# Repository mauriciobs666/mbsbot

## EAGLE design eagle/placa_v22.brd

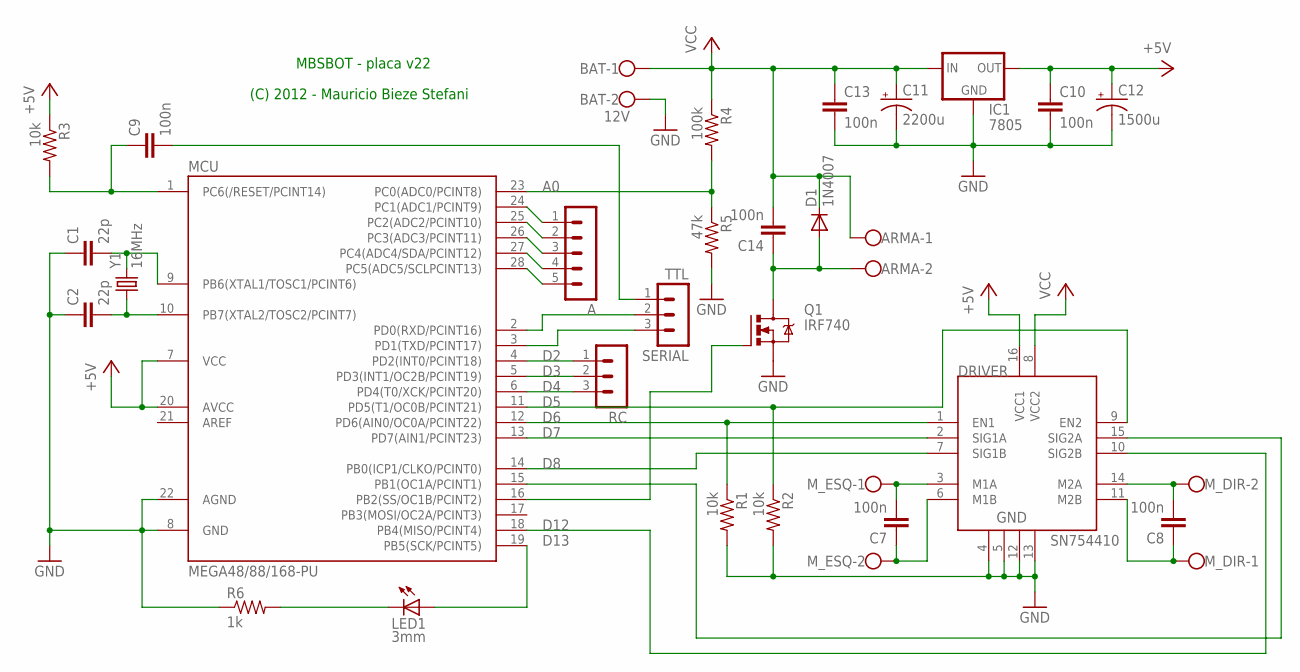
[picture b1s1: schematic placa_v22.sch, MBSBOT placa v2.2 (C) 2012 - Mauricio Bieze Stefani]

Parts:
A: MA05-1
ARMA: W237-102
BAT: 12V; W237-102; MPN 237-102
C1, C2: 22p; CAP-PTH-SMALL-KIT
C7, C8, C9, C10, C13, C14: 100n; CAP-PTH-5MM
C11: 2200u; CPOL-RADIAL-100UF-25V
C12: 1500u; CPOL-RADIAL-100UF-25V
D1: 1N4007; DIODE-1N4001
DRIVER: SN754410; DIP16
IC1: 7805; 78XXS
LED1: 3mm; LED3MM
MCU: MEGA48/88/168-PU; DIL28-3
M_DIR: W237-102
M_ESQ: W237-102
Q1: IRF740; TO220BV
R1, R2, R3: 10k; AXIAL-0.5
R4: 100k; AXIAL-0.5
R5: 47k; AXIAL-0.5
R6: 1k; AXIAL-0.3-KIT
RC: MA03-1
SERIAL: TTL; MA03-1
Y1: 16MHz; HC49US

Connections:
+5V: C10.1, C12.1 (+), DRIVER.16 (VCC1), IC1.OUT, MCU.7 (VCC), MCU.20 (AVCC), R3.P$1 (1)
A: MCU.2 (PD0(RXD/PCINT16)), SERIAL.2
A0: MCU.23 (PC0(ADC0/PCINT8)), R4.P$2 (2), R5.P$1 (1)
D2: MCU.4 (PD2(INT0/PCINT18)), RC.1
D3: MCU.5 (PD3(INT1/OC2B/PCINT19)), RC.2
D4: MCU.6 (PD4(T0/XCK/PCINT20)), RC.3
D5: DRIVER.9 (EN2), MCU.11 (PD5(T1/OC0B/PCINT21)), R2.P$1 (1)
D6: DRIVER.1 (EN1), MCU.12 (PD6(AIN0/OC0A/PCINT22)), R1.P$1 (1)
D7: DRIVER.2 (SIG1A), MCU.13 (PD7(AIN1/PCINT23))
D8: DRIVER.7 (SIG1B), MCU.14 (PB0(ICP1/CLKO/PCINT0))
D12: DRIVER.10 (SIG2B), MCU.18 (PB4(MISO/PCINT4))
D13: LED1.A, MCU.19 (PB5(SCK/PCINT5))
GND: BAT.2, C1.1, C2.1, C10.2, C11.2 (-), C12.2 (-), C13.2, DRIVER.4, DRIVER.5, DRIVER.12, DRIVER.13, IC1.GND, MCU.8 (GND), MCU.22 (AGND), Q1.S, R1.P$2 (2), R2.P$2 (2), R5.P$2 (2), R6.P$1 (1)
unnamed: LED1.K (C), R6.P$2 (2)
unnamed: C9.1, MCU.1 (PC6(/RESET/PCINT14)), R3.P$2 (2)
unnamed: C1.2, MCU.9 (PB6(XTAL1/TOSC1/PCINT6)), Y1.2
unnamed: C2.2, MCU.10 (PB7(XTAL2/TOSC2/PCINT7)), Y1.1
unnamed: C7.2, DRIVER.3 (M1A), M_ESQ.1
unnamed: C7.1, DRIVER.6 (M1B), M_ESQ.2
unnamed: C8.1, DRIVER.11 (M2B), M_DIR.1
unnamed: C8.2, DRIVER.14 (M2A), M_DIR.2
unnamed: MCU.3 (PD1(TXD/PCINT17)), SERIAL.3
unnamed: C9.2, SERIAL.1
unnamed: ARMA.2, C14.1, D1.A, Q1.D
unnamed: A.1, MCU.24 (PC1(ADC1/PCINT9))
unnamed: A.2, MCU.25 (PC2(ADC2/PCINT10))
unnamed: A.3, MCU.26 (PC3(ADC3/PCINT11))
unnamed: A.4, MCU.27 (PC4(ADC4/SDA/PCINT12))
unnamed: A.5, MCU.28 (PC5(ADC5/SCLPCINT13))
unnamed: MCU.16 (PB2(SS/OC1B/PCINT2)), Q1.G
unnamed: DRIVER.15 (SIG2A), MCU.15 (PB1(OC1A/PCINT1))
VCC: ARMA.1, BAT.1, C11.1 (+), C13.1, C14.2, D1.C, DRIVER.8 (VCC2), IC1.IN, R4.P$1 (1)

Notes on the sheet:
(C) 2012 - Mauricio Bieze Stefani
MBSBOT - placa v22

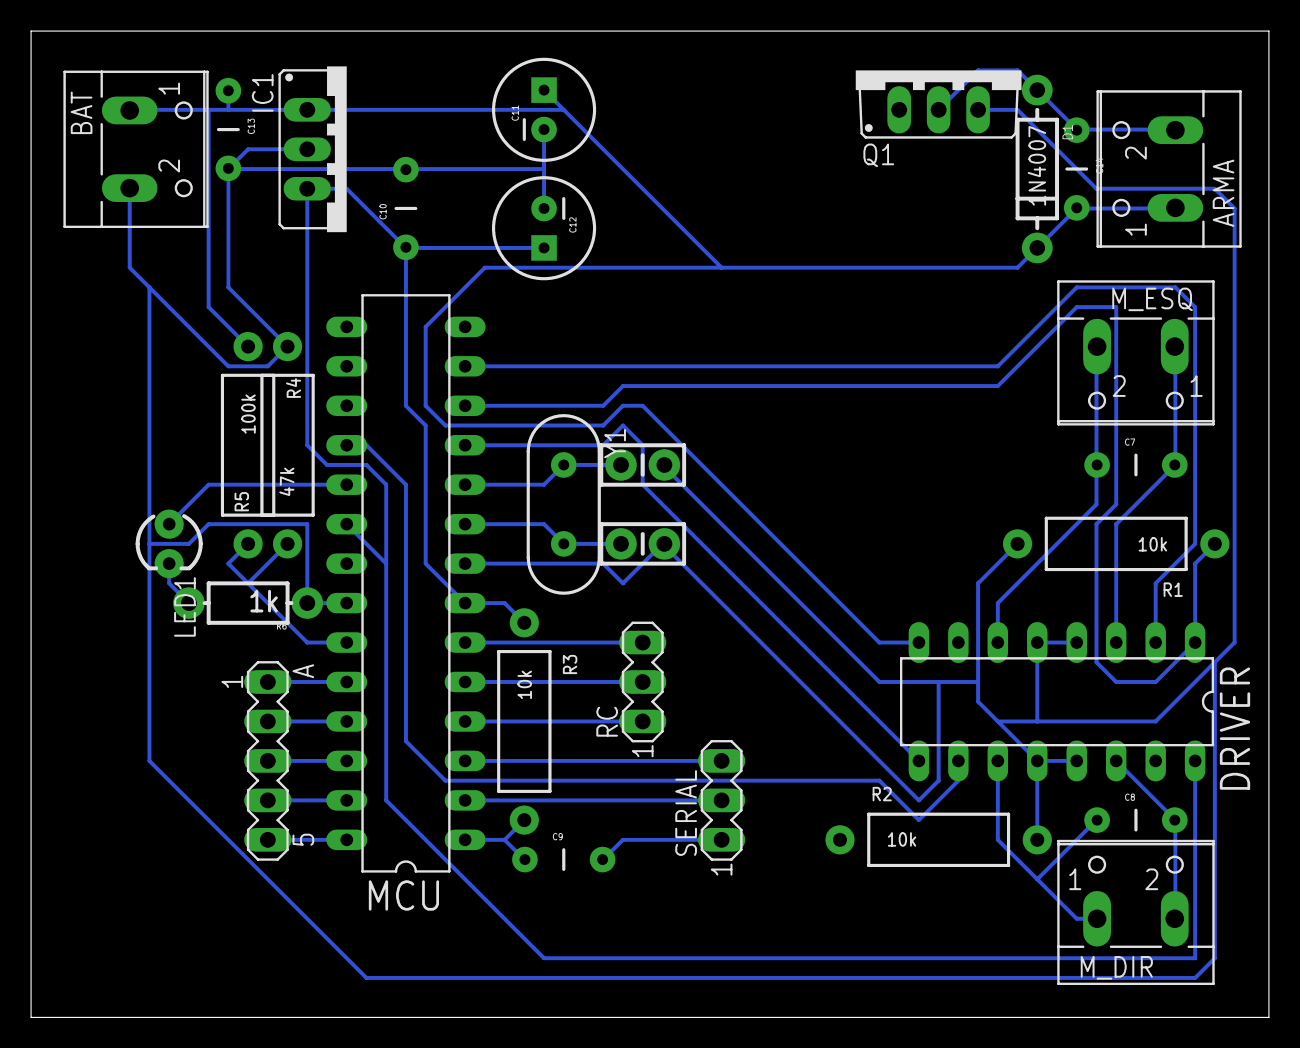
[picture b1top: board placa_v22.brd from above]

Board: 2 copper layers, 79.7 x 63.5 mm, 30 parts (0 on the bottom side), 32 nets.

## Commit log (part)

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2010-03-29 Interface improvements.
2010-04-07 Added average function to sensor analysis tab.
2010-04-08 Visual changes
2010-04-09 Added workspace
2010-04-09 Removed the preferences window. All configuration should be done in the SETUP tab.
2010-04-09 Change average algorithm to calc only last 10 measures.
2010-04-11 New prog to test 754410 chip.
2010-04-14 Small changes in the motor control shield
2010-04-15 WheelDC and drive by joystick fully working
2010-04-15 Visual and comments
2010-04-17 Small typo
2010-04-23 Unlocked full DC motor power (PWM 250). Started implementing keyboard control (core dump).
2010-05-02 Fixec core dump.
2010-05-17 Comments
2010-05-18 Missing file
2010-05-18 Improvements on joystick control Bugfixes
2010-05-18 Damn fucking servo library bitch!!!
2010-05-21 Changed DC motor pins to avoid conflict with servo lib
2010-05-21 Removed obsolet 754410 test prog Added old (arduino < 16) servo library in the hope the servo will stop jittering.
2010-05-29 Partial move files
2010-05-29 Moving files
2010-05-30 Rangefinder improvements
2010-06-01 bug fixes
2010-06-11 Created include to configure board pins
2010-06-19 Better comments.
2010-06-21 defines and comments
2010-06-22 Moved vectorial drive logic to firmware
2010-06-24 First PID scratch
2010-06-24 More PID control stuff
2010-07-01 Created new collision detector
2010-07-01 Collision detection implementation
2010-08-23 IR 5 sensor board
2010-08-31 Small details. Auto fetch status.
2010-09-02 Joystick calibration
2010-09-04 Average class
2010-09-04 Acceleration
2010-09-05 GUI improvements
2010-09-08 Bugfixes
2010-09-09 New commands left, right and set dr.
2010-09-15 Moved average to MBSUtil
2010-09-16 Program SENTRY
2010-10-14 Computer vision using OpenCV 2.1
2010-10-15 Update windows project
2010-10-17 Better timing
2010-10-25 Various
2010-10-29 Fixed servo bug
2010-11-03 Partial implementation of second and third servos.
2010-11-04 Fixed visual bug. Implemented mltiple servos in arduino side (untested).
2010-11-04 Gambiarra 2/2 (removed executable attribute from Protocol.h)
2010-11-04 QRD1114
2010-11-07 Finally able to make the wiichuck work :-)
2010-11-12 Wiichuck now able to pan & tilt servos.
2010-11-12 Various small optimizations and fixes.
2010-11-14 Bugfixes in nunchuck. Rewrote vectorial drive.
2010-11-18 Generate sensor data for "Processing" example
2010-11-22 Visual changes. New hand brake function. Placed pull down resistors on 754410 to avoid movement during start-up.
2010-11-23 Joystick handling improvements.
2010-11-24 Joystick...
2010-11-27 New widgets
2010-12-10 Removed Arduino EEPROM library dependency.
2010-12-28 Reflash script
2011-01-05 Serial port using boost tests
2011-01-05 Learning boost::program_options
2011-01-06 boost::thread
2011-01-12 Miniterminal serial fully functional (sync/thread).
2011-01-13 Threaded version... will it ever work?
2011-02-01 Arduino oscilloscope viewer
2011-02-01 Windows project
2011-02-06 Laser habilitado. Corrigido controle servos via wiichuck
2011-02-09 Rascunho direcao por wiichuck.
2011-02-10 Arduino library and Codeblocks project
2011-02-15 Removidos delays de PRG_SCOPE
2011-07-03 Pequenos fixes.
2011-11-06 cv windows
2011-11-25 Porting back pra windows 100%. Td funfando.
2011-11-25 Era uma vez um developer maneh que achava que tinha que escrever codigo em ingles. Um dia ele bateu a cabeca e voltou a escrever normal. E viveu feliz pra sempre. The end.
2011-12-07 Porting pra Arduino 1.0
2011-12-11 Depois do que aconteceu na 376346 achei melhor dar um trato no protocolo, falta coisa ainda mas tah bem melhor...
2011-12-18 Faxina
2011-12-20 Aceleracao por software pra simular inercia e tornar o controle mais suave.
2011-12-21 Bugs
2011-12-27 Diversos detalhes
2011-12-28 Muitos bugs depois... Aceleracao e controle vetorial praticamente prontos!!! :-)
2011-12-30 Nova classe Sensor
2012-01-05 Tirei todos warnings e coloquei mais umas coisinhas na classe Sensor.
2012-01-10 Copyright
2012-01-11 Diversos
2012-01-17 Alguns pequenos fixes na classe Sensor (agora funfando belezinha)
2012-01-29 Pequenos ajustes de velocidade
2012-02-01 Bug da foto
2012-02-03 Pequenas mudancas na forma que a atualizacao dos motores eh feita.
2012-02-06 Glitches...
2012-02-09 Os 2 eixos do wxJoystick agora funcionam.
2012-02-13 4 rodas mecanum funfando na gambiarra :-D Precisa rescrever um monte de coisa.
2012-02-13 Limpezinha meia boca
2012-02-28 Add no projeto
2012-03-02 Tava invertido
2012-04-15 Comecei a rescrever tratamento de joystick
2012-05-31 Coisinhas
2012-06-13 Autoversion
2012-06-18 Inicializacao automatica do joystick
2012-06-28 Bugs e to do diversos
2012-06-30 Movida implementacao de joystick pro firmware.
2012-06-30 Mais coisas do joystick
2012-06-30 x86: dropando suporte a CMD_MV_WHEELS, CMD_MV_VECT e classe de joystick. A logica agora fica 100% no firmware.
2012-07-09 Refatoracao
2012-07-10 Mais um pouquinho de refactor
2012-07-11 Projeto eagle Pequenos fixes
2012-07-14 Suporte a controlador de motor sem inversor pras pontes H. Removido variaveis deprecated.
2012-07-14 Faltou pdf...
2012-07-21 Eletronica do Winchester
2012-07-30 bla bla bla
2012-08-03 Bugfix e hardware da arma
2012-08-05 Eletronica
2012-08-09 Boberinhas
2012-08-22 Milhares de fixes
2012-09-11 Nova classe ConfigSensor pra armazenar na EEPROM. Ajustes no circuito e placa.
2012-09-18 Limite de velocidade
2012-09-25 Direcao auxiliada por sensores parcialmente implementada
2012-10-02 Porting pra v2
2012-10-04 Faxinao
2012-10-07 Bugs e reducao de binario
2012-10-09 So close...
2012-10-12 *Bugado
2012-10-14 Coisinhas, ainda bugado
2012-10-18 autoMinMax agora eh configuravel pra poder usar getPorcentoAprox em vetorialSensor
2012-10-24 ConfigGamepad
2013-03-04 Resources
2013-03-06 Bugs <3
2013-03-08 Faxinaum
2013-04-29 Pequenos ajustes da autonavegação via sensor ping
2013-05-08 Nova plava v4, line follower
2013-05-14 Rascunho da calibração da barra de sensores do line follow.
2013-05-17 Calibragem 100% Funçao de mostrar fps
2013-05-23 Bugs marditos
2013-05-27 Proporcional implementado
2013-06-08 Mergeado agrupaLinha com refresh. Muchos bugs...
2013-06-17 struct Grupo SENSOR_DIGITAL limpeza delays serial * calibra lf esta bugada nessa revisao
2013-06-22 Bugz
2013-06-28 Botao, bugs etc
2013-06-29 Diferenciador (finally) Classe botao 100%
2013-06-29 Coisinhas.
2013-07-04 Novas configuracoes de max MV, limite de acumulador, zera accumulador e debounce
2013-07-05 Deteccao de cruzamento e fim de volta
2013-07-06 Bugs bugs bugs bugs bugs arghhhhhhh
2013-07-08 Primeiro dia de provas do Winter Chalenge... :'-(
2013-07-08 Embalos de sabado a noite...
2013-07-09 Bugs do segundo dia... Tempo medido: 32,76s e 32,38s
2013-07-15 Suporte a SerialX no arduino mega.
2013-07-18 Trace
2013-07-25 Varios bugs
2013-07-29 Calibragem mais smooth com giraP()
2013-07-31 Usando classe pid
2013-08-01 Config separada de PID pra calibrar e seguir linha
2013-08-24 Pequenos ajustes visuais e gamepad.
2013-09-26 Port linux
2013-10-13 PID::gira configuravel na EEPROM
2013-10-13 Rescrevendo loop do line follow
2013-10-31 Indices no comando set pid
2013-11-06 Limpeza e nova classe Interpretador
2013-11-15 Limpeza de SRAM pro 3pi
2013-11-17 Restaurado placa Mickey ATMega1280
2013-11-20 Sensor.getReta() obsoleta. 104 bytes de RAM liberados.
2013-11-20 Mais algums bytes salvos desabilitando roda por servos
2013-11-22 Vars e atribuicao
2013-11-27 classe Variavel
2013-12-02 Reducao de memoria
2013-12-03 Atribuicao de vars
2013-12-09 Variaveis implementadas: VAR_BALANCO, VAR_VEL_MAX, VAR_VEL_ESCALA, VAR_FREIO, VAR_T_SE, VAR_T_ST, VAR_T_RF, VAR_T_MOTOR, VAR_PID_DEB
2014-06-20 Erro de build
2014-06-20 wxWidgets build adicionado como 3pp
2014-06-30 Limpeza
2014-07-06 Bug em declaraVar()
2014-07-13 Pequenos ajustes na interface grafica.
2014-07-15 Erros de comunicacao.
2014-07-18 Day zero
2014-07-19 Bug do fim da corrida e quebra de linhas
2014-07-19 Ajuste nas formulas PID Suavizacao do centro da barra de sensores
2014-07-19 Pensando bem... talvez seja melhor limitar dT e descartar D se passar de um threshold (?).
2014-07-24 Arduino 1.5.7
2014-08-02 Dropado suporte a Wiichuck. Varias otimizacoes de memoria, centenas de bytes economizados :-)
2015-02-11 upgrade Pinchangeint, varios cleanups
2015-02-20 Ponto fixo parcialmente implementado. NAO COMPILA
2015-02-21 compilando mas parcial
2015-02-22 ainda nao
2015-02-25 suporte a fixo no Interpretador
2015-02-27 calculo de posicao de linha inspirado na pololu
2015-02-27 bug interpretador
2015-02-28 mais bugs no interpretador
2015-03-04 atualizado consumo de memoria
2015-03-05 movido vetor e Fixo pra arquivo separado, rascunho de interface pro controlador baseado em rede neural
2015-03-06 teste de consumo de memoria polimorfismo
2015-03-12 ajustes na calibragem line follow e comentarios
2015-03-14 fixes em calibrar
2015-03-14 hardcoded defaults dos PIDs
2015-03-18 adaptacoes pro nano
2015-03-31 Migrating wiki contents from Google Code
2015-04-18 Fix direcao calibragem
2015-04-21 fixes
2015-04-23 dados.h e fixes
    - Configuracoes alocadas na EEPROM movidas pro arquivo dados.h
    - Fix timeout LF
    - Rascunho de suporte a matrizes no interpretador
2015-04-23 add dados.h ao projeto
2015-05-05 comandinhos hardcoded
2015-05-29 Log e obsoletos
2015-06-02 Enable Interrupt
2015-06-03 Dropado suporte a rodas servo. Encoder funfando
2015-06-03 Redefinicoes
2015-06-06 bugs (muitos)
2015-06-06 Bugs :-(
2015-06-07 aaaaa va!
2015-06-11 Mescla LineFollower::refresh e elegeTrilho
2015-06-12 Mascara de trace e revertido EnableInterrupt de volta pra PinChangeInt
2015-06-12 Encoder rescrito pra usar lib antiga PinChangeInt
2015-06-14 Eu sou brasileiro e nao desisto nunca!
2015-06-15 Buffer circular pra log
2015-06-19 Comando who e bugs ponto fixo
2015-06-21 Exercises from Andrew Ng's course on machine learning
2015-06-24 Bugs em matematica e placa 3 invertida com 4
2015-06-24 bug ridiculo na atualizacao do trilho
2015-06-26 DSM erros cruzamento, PID movido pra arquivo proprio
2015-06-30 ex2 5%
2015-06-30 ex2 70%
2015-07-02 ex2 85%
2015-07-05 Sync placas
2015-07-05 Bug deteccao cruzamento
2015-07-05 efeito colateral em calibra
2015-07-16 4x4 sem line follower
2015-08-16 Matlab - week 4.
2015-08-18 Matlab Week 5 ate ex 5
2015-08-19 matlab week 5 ex 6,7
2015-08-30 matlab week 6 ex1-3
2015-09-05 matlab week 6 - exs 4:7 10
    8 e 9 incompletos
2015-09-06 matlab week 6 ex 8
2015-10-03 matlab week 7 ex1-6
2016-09-28 placa v33
2016-12-01 altimetro
    rascunho de altimetro
2016-12-09 BMP180
2017-01-08 maior freq amostragem
    temperatura agora atualizada a apenas a cada 100ms
2017-01-09 alpha beta
2017-01-14 tracking de altitude de DZ e PS
2017-01-27 aviso de altura
2017-02-10 possivel crash. removidos traces por performance
2017-02-11 unificacao e bugfixes
2017-02-19 crash fix, trace a cada segundo
2017-03-01 bug: threshold velocidade queda livre/abertura tava muito baixo
2017-03-10 migracao interpretador
2017-03-11 config a ser jumpado 11/3
2017-03-19 bug avisos e melhor precisao no sensor ao ler temp sempre
2017-03-21 a ser jumpado 21/3
2017-07-15 hot fix abertura subterminal e sirene
2017-07-21 a ser jumpado 22/7/17
2017-10-16 movida classe tocador pra arquivo tocador.hpp
2017-10-24 eeprom, interpretador
2017-10-25 fim de salto e log
2017-10-31 update na eeprom e bugfixes
2017-11-02 a ser jumpado 3/11/17
2017-11-11 clean-up, bugs de 3/11 ainda pendentes
2017-11-24 a ser jumpado 25/11/17
2017-11-26 ajuste threshold subterminal
2017-12-16 otimizacoes de consumo de memoria
2018-07-04 bug registro pouso durante espera pra lancamento
    a ser testado 9/7
2018-07-04 bug velocidade max navegacao e altitude de saida
    a ser jumpado 9/7
2018-08-03 inconsistencia abertura X saida em subterminal
2018-08-06 arduino mega + sdcard
2019-06-06 algumas limpezas algumas porquices
    fds
2019-06-10 SD card funfando
2019-06-16 Refactoring e bugs
2019-06-25 botao liga/desliga bluetooth
2019-06-26 teste de buzzer
2019-07-05 placa nova :-)
2019-07-21 2 sensores (inicio)
2019-07-22 2 sensores pt 2
2019-07-23 url lib toneAC
2019-07-23 Warnings compilador linux
2019-08-04 2 arquivos pt2
2019-08-04 back porting micro
2019-08-04 warnings
2019-08-13 producao

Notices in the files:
parts and their libraries:
SparkFun: Licensing: CC v3.0 Share-Alike You are welcome to use this library for commercial purposes.
